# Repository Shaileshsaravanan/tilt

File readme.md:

Galvanic Vestibular Stimulation (GVS)

custom galvanic vestibular stimulation device to control/hack your balance

## context

galvanic vestibular stimulation (gvs) delivers low-current dc signals (1-2 ma) across the mastoid processes to hack your balance. the cathode depolarizes the vestibular nerves to increase their firing rate, while the anode hyperpolarizes them to decrease it. your brain perceives this mismatch as physical tilt, forcing your body to instinctively lean toward the anode to compensate.

## schematic

1. control (esp-01)
   generates complementary pwm and direction signals. gpio0 and gpio2 need pull-up/pull-down resistors to force a known safe state during bootup so they don't float and trigger the stimulation rail on power-up

2. power boost (mt3608)
   steps up 3.7v input to a stable 12v-15v rail. this high headroom is required to break through skin-electrode impedance, which easily sits around 5k-10k ohms on dry skin

3. galvanic isolation
   optoisolators decouple the microcontroller's logic from the stimulation stage. this shields your head from any potential mains-side faults or grounding issues if you ever plug the esp-01 into a usb port to debug

4. active constant-current regulation
   the critical safety gate. uses an lm334 or a closed-loop feedback op-amp to clamp the current to a strict 1.5ma-2ma. this overrides the dynamic drop in skin resistance so you don't get a sudden, uncontrolled current spike

5. h-bridge polarity control
   uses a matched array of 2n3906 (pnp) and 2n3904 (npn) transistors. dynamically reverses the current path across the electrode array, swapping which mastoid acts as the cathode and which acts as the anode for left/right tilt

## pcb

i just wanted a non rectangular shaped pcb so i just made it into a random polygon

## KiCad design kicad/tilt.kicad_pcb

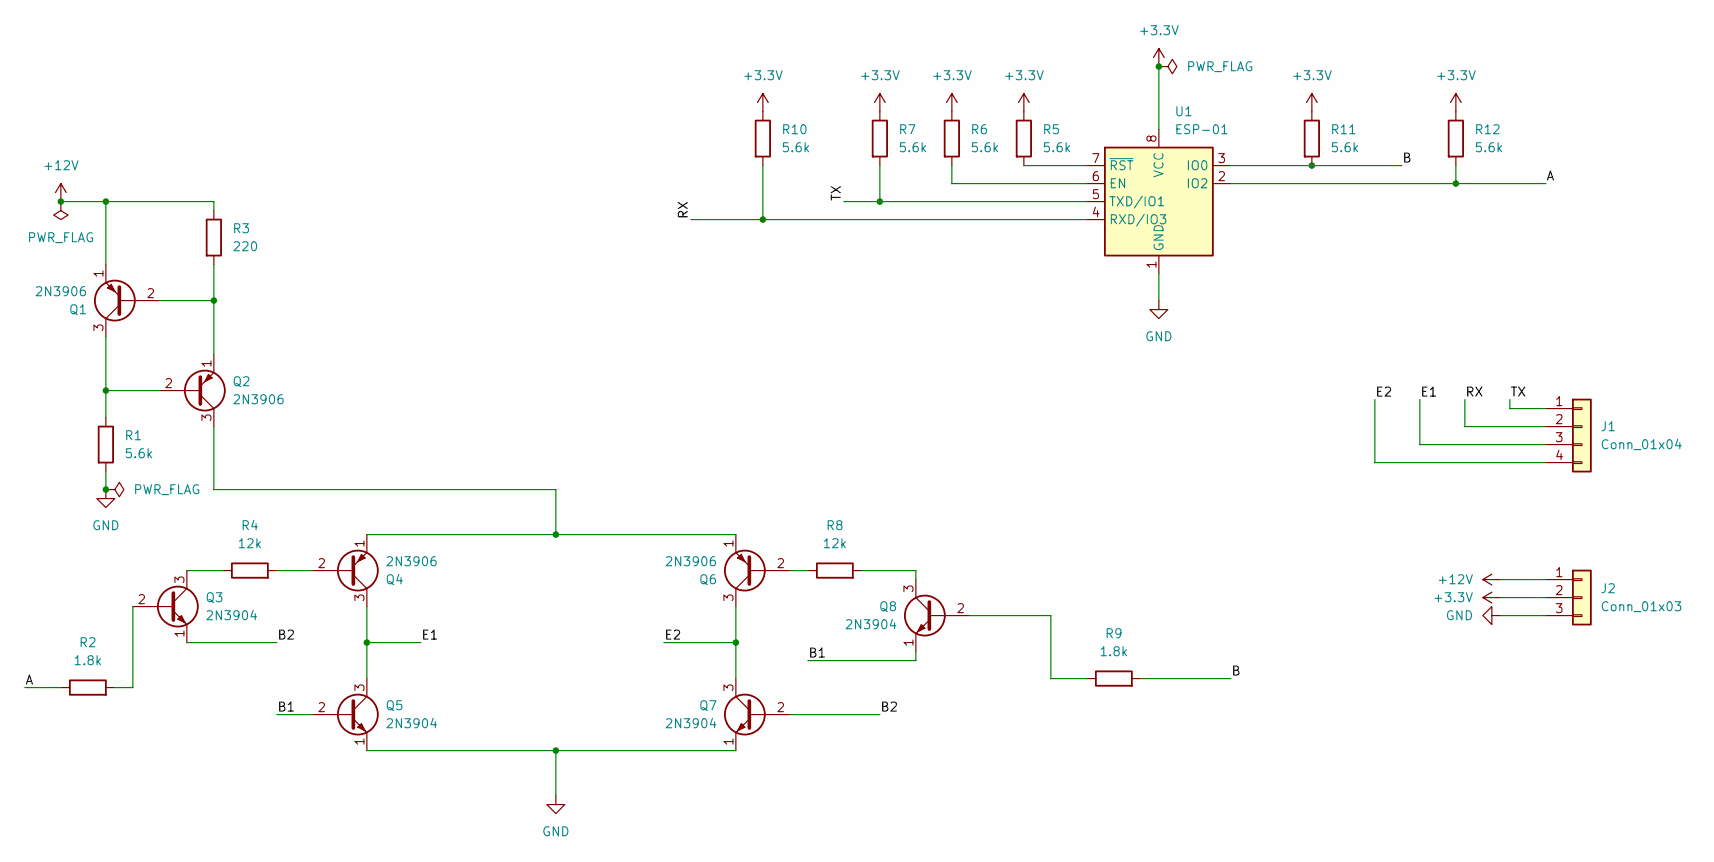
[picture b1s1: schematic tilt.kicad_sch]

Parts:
J1: Conn_01x04; PinHeader_1x04_P2.54mm_Vertical
J2: Conn_01x03; PinHeader_1x03_P2.54mm_Vertical
Q1, Q2, Q4, Q6: 2N3906; TO-92_Inline
Q3, Q5, Q7, Q8: 2N3904; TO-92_Inline
R1, R5, R6, R7, R10, R11, R12: 5.6k; R_Axial_DIN0207_L6.3mm_D2.5mm_P10.16mm_Horizontal
R2, R9: 1.8k; R_Axial_DIN0207_L6.3mm_D2.5mm_P10.16mm_Horizontal
R3: 220; R_Axial_DIN0207_L6.3mm_D2.5mm_P10.16mm_Horizontal
R4, R8: 12k; R_Axial_DIN0207_L6.3mm_D2.5mm_P10.16mm_Horizontal
U1: ESP-01

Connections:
+3.3V: J2.2, R5.1, R6.1, R7.1, R10.1, R11.1, R12.1, U1.8 (VCC)
+12V: J2.1, Q1.1 (E), R3.1
/A: R2.1, R12.2, U1.2 (IO2)
/B: R9.2, R11.2, U1.3 (IO0)
/B1: Q5.2 (B), Q8.1 (E)
/B2: Q3.1 (E), Q7.2 (B)
/E1: J1.3, Q4.3 (C), Q5.3 (C)
/E2: J1.4, Q6.3 (C), Q7.3 (C)
/RX: J1.2, R10.2, U1.4 (RXD/IO3)
/TX: J1.1, R7.2, U1.5 (TXD/IO1)
GND: J2.3, Q5.1 (E), Q7.1 (E), R1.2, U1.1 (GND)
unnamed: Q1.2 (B), Q2.1 (E), R3.2
unnamed: Q1.3 (C), Q2.2 (B), R1.1
unnamed: Q2.3 (C), Q4.1 (E), Q6.1 (E)
unnamed: Q3.2 (B), R2.2
unnamed: Q3.3 (C), R4.1
unnamed: Q4.2 (B), R4.2
unnamed: Q6.2 (B), R8.1
unnamed: Q8.2 (B), R9.1
unnamed: Q8.3 (C), R8.2
unnamed: R6.2, U1.6 (EN)
unnamed: R5.2, U1.7 (~RST)

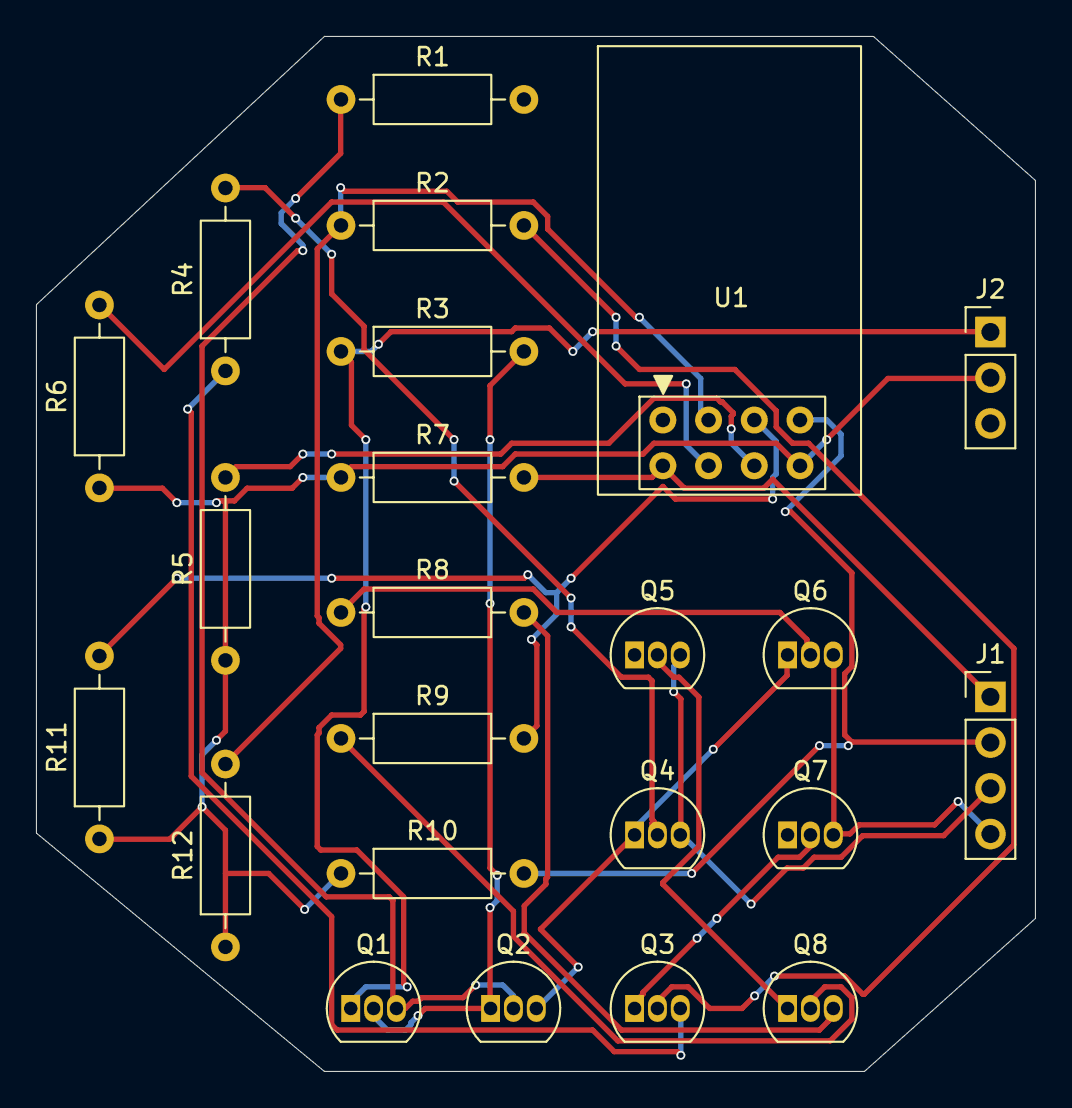
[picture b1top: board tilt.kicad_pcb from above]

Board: 2 copper layers, 55.5 x 57.5 mm, 23 parts (0 on the bottom side), 22 nets.

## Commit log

2026-06-24 base
2026-06-26 updated readme + kicad folder
2026-06-30 added bom.csv
